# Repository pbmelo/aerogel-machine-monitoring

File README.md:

# aerogel-machine-monitoring

This repository is meant to be a place where I'm able to control and keep my
files for a remote monitoring system I have developed for a critical point drying machine.

## Note

The files hosted here are under active development and have some minor issues.
I expect to keep updating the repository with improvements as well as a detailed
guide on how to use and reproduce it yourself.

## What is required to build a similar system

1. An Arduino or similar controller
2. As many thermocouples as wanted (0 to 5)
3. Adafruit's max31856 thermocouple current amplifier (one per thermocouple)
4. As many pressure transducers that operate in a 4..20 mA fashion as wanted
   (0 to 5)
5. As many electrically operated pneumatic valves as wanted (0-4)
6. Generic 5V relays (one per pneumatic valve)
7. A computer that will host the web interface and talk to the Arduino board (if
   a web interface is desired)

## Contents

This repository contains

1. Source code for the Arduino board to monitor temperature and pressure
   sensors, as well as control relays
2. Required files for a system on a chip (such as Raspberry Pi) or any other
   computer, such as the following:
3. A systemd service that communicates with the Arduino to read its output and
   write it to a file, to be later used by the web server
4. Source code for the web interface that controls the Arduino.  Namely, read
   the output file, display the data to the user interface, grab user commands
   from the interface and send them to the Arduino
5. Instructions on how to wire the system and set the software up

### To do

My future plans consist of

1. Improve the performance and overall user experience of the web interface
2. Write a detailed tutorial on how to set everything up
3. Make a Raspberry Pi, other arm32/64, as well as an x86_64 image with
   everything pre configured, such that the end user will just have to clone
   them to disk
4. Upload pictures of the web interface as well as printed circuit, together
   with a short usage manual (it's all very intuitive, really!)
5. Design and upload a 3D printed case for the whole system

### Images

Here's how the system looks after being soldered and assembled

## LICENSE

Copyright (C) 2022 pbmelo

This program is free software: you can redistribute it and/or modify it under
the terms of the GNU General Public License as published by the Free Software
Foundation, either version 3 of the License, or (at your option) any later
version.

This program is distributed in the hope that it will be useful, but WITHOUT ANY
WARRANTY; without even the implied warranty of MERCHANTABILITY or FITNESS FOR A
PARTICULAR PURPOSE. See the GNU General Public License for more details.

You should have received a copy of the GNU General Public License along with
this program. If not, see <https://www.gnu.org/licenses/>.

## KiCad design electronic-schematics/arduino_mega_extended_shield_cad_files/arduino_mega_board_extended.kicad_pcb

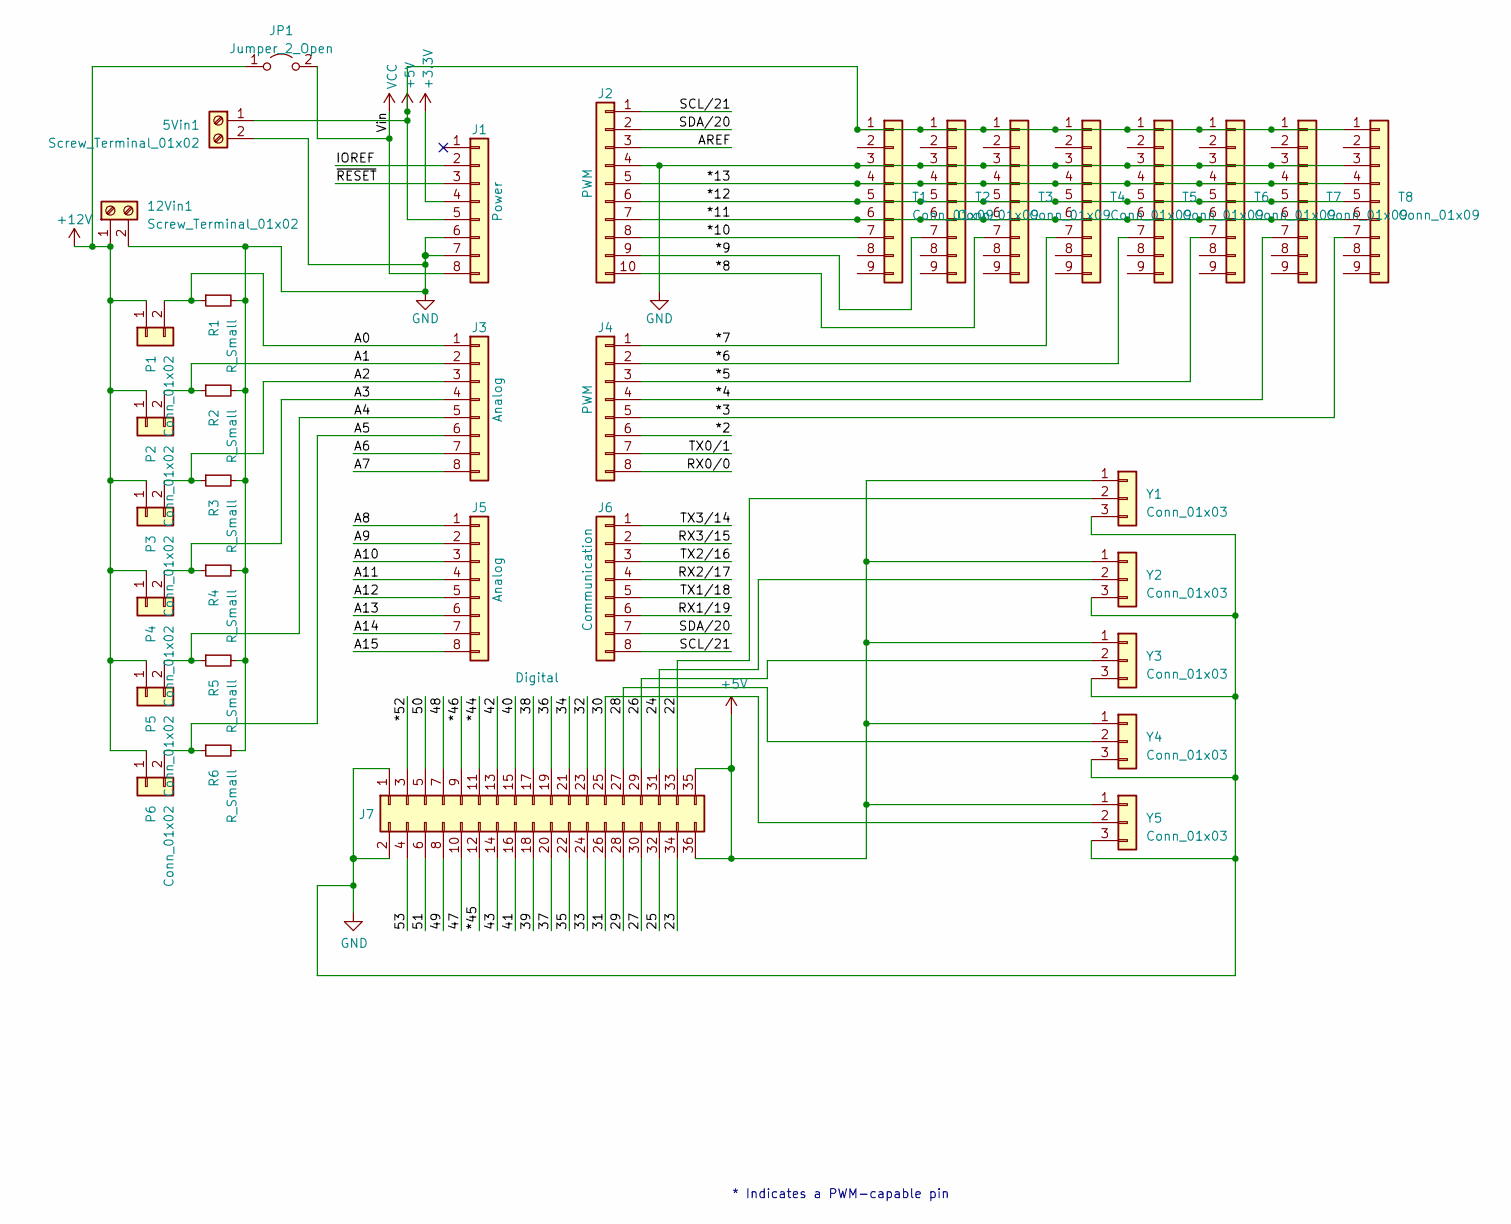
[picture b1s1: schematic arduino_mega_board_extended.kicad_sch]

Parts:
5Vin1, 12Vin1: Screw_Terminal_01x02; TerminalBlock_Phoenix_MKDS-1,5-2-5.08_1x02_P5.08mm_Horizont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
J1: Power; PinSocket_1x08_P2.54mm_Vertical
J2: PWM; PinSocket_1x10_P2.54mm_Vertical
J3, J5: Analog; PinSocket_1x08_P2.54mm_Vertical
J4: PWM; PinSocket_1x08_P2.54mm_Vertical
J6: Communication; PinSocket_1x08_P2.54mm_Vertical
J7: Digital; PinSocket_2x18_P2.54mm_Vertical
JP1: Jumper_2_Open; PinHeader_1x02_P2.54mm_Vertical
P1, P2, P3, P4, P5, P6: Conn_01x02; PinHeader_1x02_P2.54mm_Vertical
R1, R2, R3, R4, R5, R6: R_Small; R_Axial_DIN0309_L9.0mm_D3.2mm_P12.70mm_Horizontal
T1, T2, T3, T4, T5, T6, T7, T8: Conn_01x09; PinHeader_1x09_P2.54mm_Vertical
Y1, Y2, Y3, Y4, Y5: Conn_01x03; PinHeader_1x03_P2.54mm_Vertical

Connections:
+3V3: J1.4
+5V: 5Vin1.1, J1.5, J7.35, J7.36, T1.1, T2.1, T3.1, T4.1, T5.1, T6.1, T7.1, T8.1, Y1.1, Y2.1, Y3.1, Y4.1, Y5.1; also elsewhere on the board
+12V: 12Vin1.1, JP1.1 (A), P1.1, P2.1, P3.1, P4.1, P5.1, P6.1; also elsewhere on the board
/23: J7.34
/25: J7.32
/27: J7.30
/29: J7.28
/31: J7.26
/32: J7.23
/33: J7.24
/34: J7.21
/35: J7.22
/36: J7.19
/37: J7.20
/38: J7.17
/39: J7.18
/40: J7.15
/41: J7.16
/42: J7.13
/43: J7.14
/47: J7.10
/48: J7.7
/49: J7.8
/50: J7.5
/51: J7.6
/53: J7.4
/*2: J4.6
/*3: J4.5, T8.7
/*4: J4.4, T7.7
/*5: J4.3, T6.7
/*6: J4.2, T5.7
/*7: J4.1, T4.7
/*8: J2.10, T3.7
/*9: J2.9, T2.7
/*10: J2.8, T1.7
/*11: J2.7, T1.6, T2.6, T3.6, T4.6, T5.6, T6.6, T7.6, T8.6
/*12: J2.6, T1.5, T2.5, T3.5, T4.5, T5.5, T6.5, T7.5, T8.5
/*13: J2.5, T1.4, T2.4, T3.4, T4.4, T5.4, T6.4, T7.4, T8.4
/*44: J7.11
/*45: J7.12
/*46: J7.9
/*52: J7.3
/A0: J3.1, P1.2, R1.1
/A1: J3.2, P2.2, R2.1
/A2: J3.3, P3.2, R3.1
/A3: J3.4, P4.2, R4.1
/A4: J3.5, P5.2, R5.1
/A5: J3.6, P6.2, R6.1
/A6: J3.7
/A7: J3.8
/A8: J5.1
/A9: J5.2
/A10: J5.3
/A11: J5.4
/A12: J5.5
/A13: J5.6
/A14: J5.7
/A15: J5.8
/AREF: J2.3
/IOREF: J1.2
/RX0/0: J4.8
/RX1/19: J6.6
/RX2/17: J6.4
/RX3/15: J6.2
/SCL/21: J2.1, J6.8
/SDA/20: J2.2, J6.7
/TX0/1: J4.7
/TX1/18: J6.5
/TX2/16: J6.3
/TX3/14: J6.1
/~RESET: J1.3
GND: 5Vin1.2, 12Vin1.2, J1.6, J1.7, J2.4, J7.1, J7.2, R1.2, R2.2, R3.2, R4.2, R5.2, R6.2, T1.3, T2.3, T3.3, T4.3, T5.3, T6.3, T7.3, T8.3, Y1.3, Y2.3, Y3.3, Y4.3, Y5.3; also elsewhere on the board
VCC: J1.8, JP1.2 (B)

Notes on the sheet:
* Indicates a PWM-capable pin

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
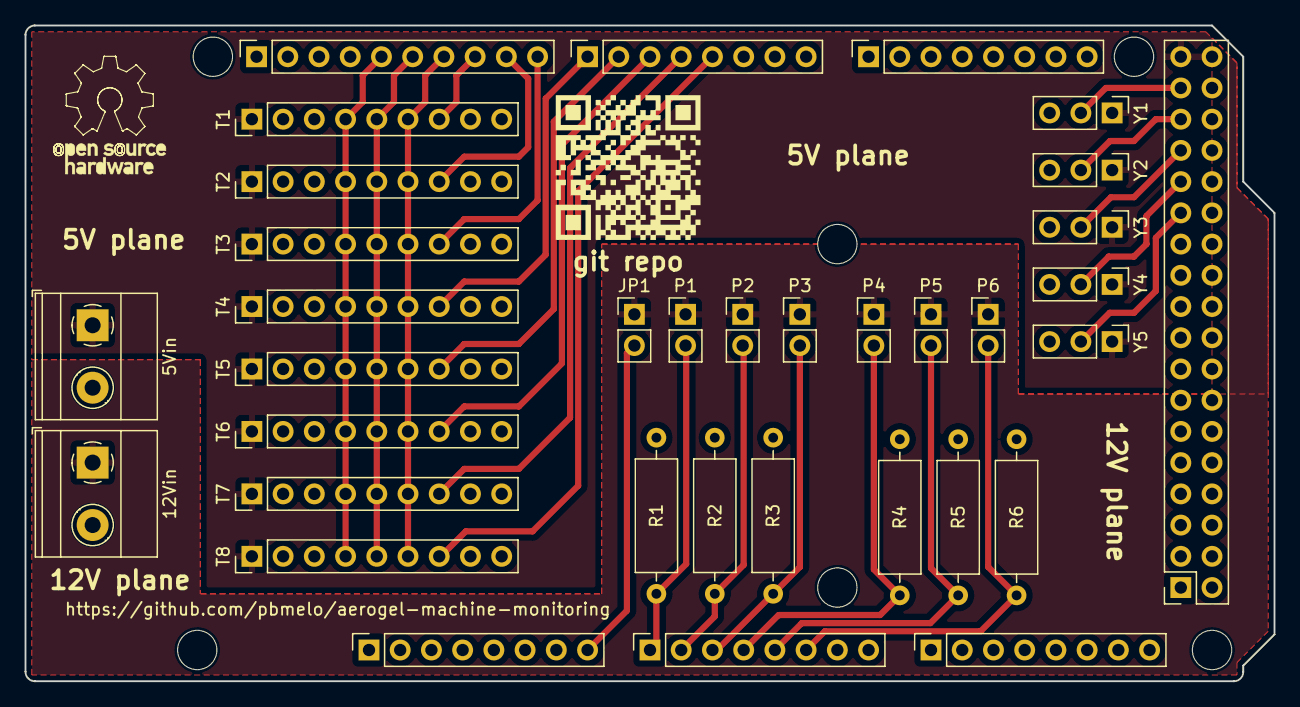
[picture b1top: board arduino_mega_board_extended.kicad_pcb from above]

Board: 2 copper layers, 101.6 x 53.3 mm, 43 parts (1 on the bottom side), 28 nets.

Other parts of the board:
5Vin, 12Vin: Screw_Terminal_01x02; TerminalBlock_Phoenix_MKDS-1,5-2-5.08_1x02_P5.08mm_Horizont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
MH1, MH2, MH3, MH4, MH5, MH6: MountingHole_3.2mm
git repo: LOGO; qrcode-aerogel-github-kicad-footprint-small
git repo#2: LOGO; qrcode-aerogel-github-kicad-footprint-small

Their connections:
+5V: 5Vin.1; also elsewhere on the board
+12V: 12Vin.1; also elsewhere on the board
GND: 5Vin.2, 12Vin.2; also elsewhere on the board

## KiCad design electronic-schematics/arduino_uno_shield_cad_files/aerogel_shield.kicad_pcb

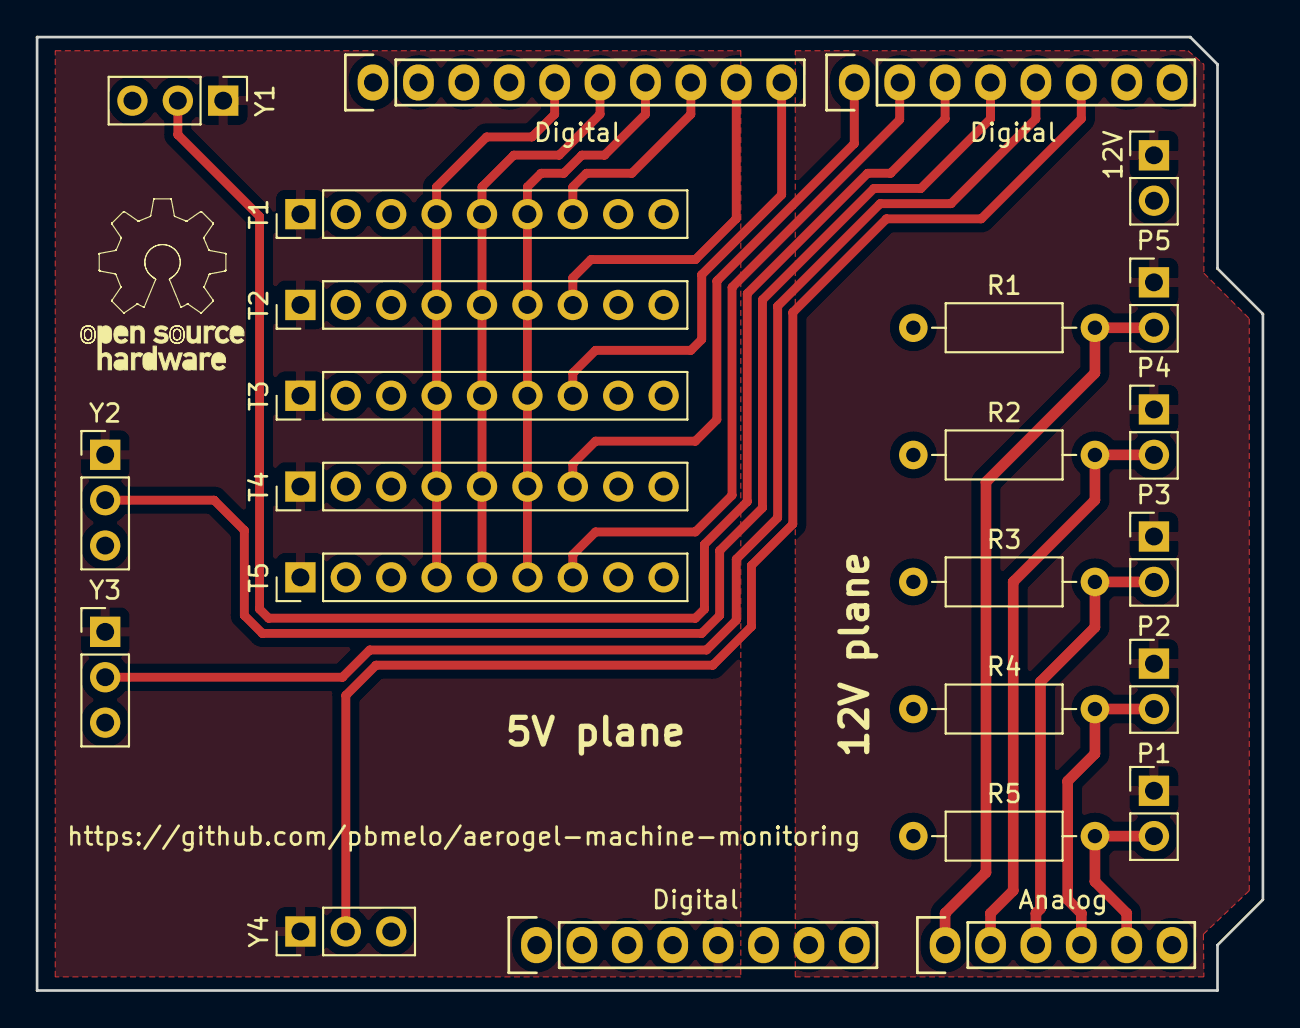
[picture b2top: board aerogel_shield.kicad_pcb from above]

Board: 2 copper layers, 68.6 x 53.3 mm, 24 parts (0 on the bottom side), 21 nets.

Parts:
12V: Conn_01x02_Female; PinHeader_1x02_P2.54mm_Vertical
Analog: Analog; Socket_Strip_Arduino_1x06
Digital: Power; Socket_Strip_Arduino_1x08
Digital#2: Digital; Socket_Strip_Arduino_1x10
Digital#3: Digital; Socket_Strip_Arduino_1x08
P1, P2, P3, P4, P5: Conn_01x02_Male; PinHeader_1x02_P2.54mm_Vertical
R1, R2, R3, R4, R5: R; R_Axial_DIN0207_L6.3mm_D2.5mm_P10.16mm_Horizontal
T1, T2, T3, T4, T5: Conn_01x09_Male; PinHeader_1x09_P2.54mm_Vertical
Y1, Y2, Y3, Y4: Conn_01x03_Female; PinHeader_1x03_P2.54mm_Vertical

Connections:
+5V: Digital.5, T1.1, T2.1, T3.1, T4.1, T5.1, Y1.1, Y2.1, Y3.1, Y4.1
+12V: 12V.1, P1.1, P2.1, P3.1, P4.1, P5.1
/2: Digital#3.6, Y4.2
/3(**): Digital#3.5, Y3.2
/4: Digital#3.4, Y2.2
/5(**): Digital#3.3, Y1.2
/6(**): Digital#3.2, T5.7
/7: Digital#3.1, T4.7
/8: Digital#2.10, T3.7
/9(**): Digital#2.9, T2.7
/10(**/SS): Digital#2.8, T1.7
/11(**/MOSI): Digital#2.7, T1.6, T2.6, T3.6, T4.6, T5.6
/12(MISO): Digital#2.6, T1.5, T2.5, T3.5, T4.5, T5.5
/13(SCK): Digital#2.5, T1.4, T2.4, T3.4, T4.4, T5.4
/A0: Analog.1, P5.2, R1.2
/A1: Analog.2, P4.2, R2.2
/A2: Analog.3, P3.2, R3.2
/A3: Analog.4, P2.2, R4.2
/A4(SDA): Analog.5, Digital#2.2, P1.2, R5.2
/A5(SCL): Analog.6, Digital#2.1
GND: 12V.2, Digital.6, Digital.7, Digital#2.4, R1.1, R2.1, R3.1, R4.1, R5.1, T1.3, T2.3, T3.3, T4.3, T5.3, Y1.3, Y2.3, Y3.3, Y4.3

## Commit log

2022-02-06 uploading the repository
2022-02-11 increase track width on gerber files, add screenshots, update readme
2022-02-15 improving cad files
2023-02-17 Adding Arduino Mega board CAD files, extended version with more connections for extra sensors
2023-02-21 Fixing project files for Mega shield. Adding gerber files for Mega shield. Adding screenshots for Mega shield and web interface. Changing some file names.
2023-02-21 Updating web interface. Updating arduino code for uno shield.
2023-05-02 adding images of the complete pcb
2023-05-02 adding photo of fully assembled printed circuit board to readme
2023-05-02 fixing readme
2023-09-29 updating readme.md
